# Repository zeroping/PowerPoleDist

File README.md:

# PowerPoleDist

An Anderson PowerPole DC power distribution box.

## What is this thing?

Amateur radio hobbyists (among others) have lots of electronic gear running off of 12 VDC, and to keep the wiring a little cleaner, many of them use PowerPole connectors from Anderson Power Products. These handy little connectors can handle up to 45 amps, and have become a defacto standard.

One of the common accessories is a power breakout, basically a “power strip” for these 12 V connections. These are available from several vendors for under $100, but I wanted some slightly different features (namely, right-angle connectors), so I designed my own.

It can handle at least 30 amps, but past that, you might want to order the PCB with 2 oz/inch copper, or solder copper wires to the PCB to lower the trace resistance.

This design is as open as I can easily make it, so if you want to change something, add something, etc, you can. The one catch is that I don't have the full 3D models for the case published (license issues), but I do have the resulting 2D shapes, so you can order your own case or make simple modifications.

The documentation should be viewable in [a pretty format on Github Pages](https://zeroping.github.io/PowerPoleDist/), or [directly in the GitHub project directory along side all the source files](https://github.com/zeroping/PowerPoleDist).

## What does it take to build one?

This design consists of:
- A custom circuit board that you can order online (design files provided)
- Electronic components that you can order from most suppliers (I used Digikey)
- A few harder-to-get components (the power connectors) available from more specialized shop (I used [Powerwerx](https://powerwerx.com/anderson-power-powerpole-sb-connectors))
- An aluminum case that you can order from a place like SendCutSend (design files provided)
- Some spacers and bolts and such that you can order from a mechanical parts supplier (I used McMaster-Carr)
 
It takes some through-hole soldering and some assembly, but the largest issue with the design is the shipping costs and one-time costs for the custom parts. The parts cost is around $30 per system, but you could easily spend three times that if you ordered just one of these, since you’re buying and shipping parts from five different vendors.

As a result, I think this design is most useful for someone building several for all their amateur radio friends, or someone who is looking for a design to modify or extend.

## Ordering Components

###  PCB files

The PCB production files are in the PCB/gerbers directory. You should be able to use the zip file as-is for most PCB manufacturers. I recommend the wonderful [PCB Shopper](https://pcbshopper.com/) to price-compare for a 2-layer, 40 x 130mm board. You might want to [check for any github issues](https://github.com/zeroping/PowerPoleDist/issues) before you order.

The original PCB design files are in the [PCB directory](https://github.com/zeroping/PowerPoleDist/tree/master/PCB). It's designed in the open-source PCB design package [KiCad](https://kicad.org/).

### Components

A reasonable list of the parts and costs [is available here](https://github.com/zeroping/PowerPoleDist/raw/master/Docs/PowerPole_Distribution_Board_Costs.ods).

You can order all of these parts [from Digi-Key using this cart link] (https://www.digikey.com/short/zb19f1), but you may want to order the [Anderson PowerPole parts from Powerwerx](https://powerwerx.com/anderson-power-powerpole-sb-connectors) to get better prices. The links are also in [the parts list spreadsheet](https://github.com/zeroping/PowerPoleDist/raw/master/Docs/PowerPole_Distribution_Board_Costs.ods).

You'll also want to add some [Mini/APM/ATM fuses](https://www.digikey.com/product-detail/en/eaton-bussmann-electrical-division/BK-ATM-30/283-2332-ND/264848) of whatever rating you want.

They're not necessary or 100% perfect, but I've been using [these rubber feet on Amazon](https://www.amazon.com/gp/product/B07LCMS23S/ref=ppx_yo_dt_b_search_asin_title?ie=UTF8&psc=1).

### Case

The case can be ordered by uploading the files in the [Mechanical directory](https://github.com/zeroping/PowerPoleDist/tree/master/Mechanical) to a place like [SendCutSend](https://sendcutsend.com/), in one of their 0.063” / 1.6 mm materials. I used their [5052 Aluminum](https://sendcutsend.com/aluminum/), and these are tight-fit parts, so you might want to adjust the files a tad for other materials. Be aware that they currently have a $29 minimum per material, so either order more than one, or see what else you want to get cut from metal.

There are also some M3 screws, spacers, and nuts that hold the whole thing together. I ordered these from [McMaster-Carr](https://www.mcmaster.com/), but they all come in packs of 100 – you wanted to build 25 of these, right? The links are available in [the parts list spreadsheet](https://github.com/zeroping/PowerPoleDist/raw/master/Docs/PowerPole_Distribution_Board_Costs.ods).

## Assembly

Start by putting the right-angle contacts into the Anderson PowerPole housings, and slotting the red and black housings side by side. Be sure to check which side the red goes on!

Next, solder the high-current components into the board: the PowerPole contacts, and the fuse holders. These will all take a bit of heat from your soldering iron due to the large traces, and will take lots of solder. I haven’t managed to use too much solder yet. The fuse holders particularly don’t like to wick solder to their surfaces without enough solder on them.

I recommend using some clever supporting on a heat-resistant surface to get all of these parts held in place while you solder them. You especially want to make sure the PowerPole contacts aren’t in crooked.

Then, solder all of the smaller through-hole components. This should be relatively straight forward.

The LEDs can be soldered directly on the board, or you can raise them up to get them to poke through the top of the case. If you raise them up, I recommend measuring and cutting 10 little scraps of wire insulation, and using that wire insulation to get the LEDs at the right height. Since the PCB silkscreen isn't super clear, the flat side / short leg of the LED goes away from the PowerPoles.

Decide if you want the LEDs to be on all the time, or just when you press the fuse check button. If you want them on all the time, short JP1 with some solder. Be aware, the current-limiting resistors for the LEDs were chosen to be pretty bright, so you might choose larger resistances for R1-R10 if you want them on all the time.

Also decide if you want the case connected to GND. If you do, then short jumper JP101 with some solder. I don’t recommend it, as the fuses will probably short 12V to the case if you decided to unplug one of them while the system is powered.

Next, start assembling the case. Start by threading the ‘front’ panel down between the PowerPole housings. This panel is just barely not reversible – the PowerPole housings are slight off-center and closer to the end of the board with the tactile switch. Add that to the list of fixes for the next version!

Once you have the front panel in place, you can put the top on, threading the LEDs in place as as you go. You can start to fit the front panel into the top by tapping it gently with a hammer. This aluminum will bend if you’re not careful, but it makes for a satisfyingly tight fit when it goes together.

This is now your last chance to check everything over and put the spacers in before you finish assembling the case. The taller spacers go on the top of the board, and the shorter ones go below, so put those in place, and thread the long M3 screws through the case top, the spacers, and PCB. From this point on, you will want to leave the M3 screws in place to keep the spacers lined up. You might want to  put the nuts on for now to hold them in place. It is quite annoying to have to disassemble the case to re-position a spacer.

Now, add the case back and sides. Again, you might want to use a hammer to tap them in. Use a board edge or something to let you put the "top" against a firm, flat surface, since there are now M3 screw heads sticking out of the top.

At this point, you can take the M3 nuts back off and add the case bottom. You might want to again thread the M3 nuts on to hold the screws in place while you tap the aluminum together.

Once you get the case all slotted together, you can try adding rubber feet. The ones I found don’t fit perfectly, but they squish just enough to let these nuts thread on to the M3 screw. I have found that squishing the feet (with nuts in place) just a little bit helps me get it started, and after that, the nuts seem to lock in place enough to let you tighten them. I’d like to have better feet, but these are the best ones I’ve found that are cheap.

## Issues

Github has a way to handle [reporting issues](https://github.com/zeroping/PowerPoleDist/issues), so submit any problems there, and look there for issues that other people have hit. The nice thing about handling it here is that, even if I'm not attentive, at least the issues will all be public.

## Reuse of this design

I want this design to be open for anyone to use for hobbiest use. If you’re selling them for a profit, give me some attribution and link to this git repo. If you’re selling more than 100 for a profit, let me know - I will probably still be ok with it.

I’ll work on picking a proper license at some point, but for now, just be reasonable.

## Other references

In the very least, I wanted to point out an [alternative PowerPole distribution board by Tyler Ward, M0UAV, over on hackaday.io](https://hackaday.io/project/10489-powerpole-distribution-block). His version uses the vertical PowerPole PCB terminals, and an acrylic case, but is otherwise very similar.

I know there are a fair number of amateur radio users who are using 4-cell LiFePo4 batteries for portable DC power sources, so I'll also mention [Alex Klimaj's LiPow USB-C battery charger](https://hackaday.io/project/161771-lipow-the-usb-c-lipo-battery-charger). It doesn't support LiFePo4 chemistry right out of the box, but it's an interesting and unique design that I'm likely to use in the future for charging my home-built battery pack.

If you have a related open hardware design, let me know, and I might add a link to it here.

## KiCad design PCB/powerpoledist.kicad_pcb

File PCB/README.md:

These are the files for the circuit board, designed in KiCAD 5.0.2. There are a couple of custom libraries that I made for the Anderson PowerPole right-angle connectors and the fuse holders, but they should be included here. 

Note that there are two parallel versions of many of the fust check components - this lets you build the board using either through-hole or surface-mount components, but I recommend the through-hole components if you're building the boards as one-offs.

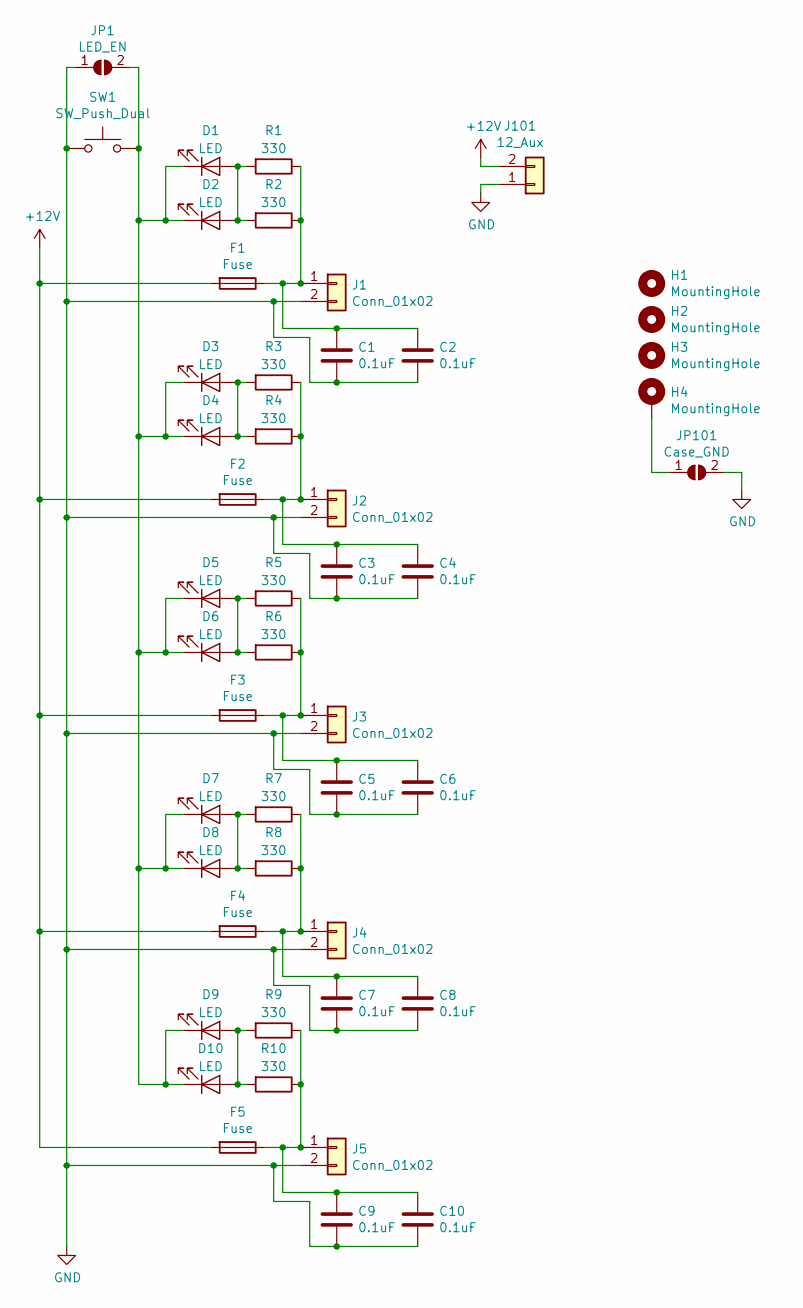
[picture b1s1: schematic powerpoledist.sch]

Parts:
C1, C3, C5, C7, C9: 0.1uF; C_0805_2012Metric_Pad1.15x1.40mm_HandSolder; MPN C0805C104M3RACTU
C2, C4, C6, C8, C10: 0.1uF; C_Disc_D3.8mm_W2.6mm_P2.50mm; MPN K104Z15Y5VE5TL2
D1, D3, D5, D7, D9: LED; D_0805_2012Metric_Pad1.15x1.40mm_HandSolder; MPN LTST-S220GKT
D2, D4, D6, D8, D10: LED; LED_D3.0mm; MPN INL-3AR30
F1, F2, F3, F4, F5: Fuse; Fuseholder_Blade_Mini_Keystone_3557_Slots; MPN 3557
H1, H2, H3, H4: MountingHole; MountingHole_3.5mm_Pad_Via
J1, J2, J3, J4, J5: Conn_01x02; PowerPole_PP45_1336G1_1x2_Horizontal; MPN 1336G1
J101: 12_Aux; PinHeader_1x02_P2.54mm_Vertical
JP1: LED_EN; SolderJumper-2_P1.3mm_Open_RoundedPad1.0x1.5mm
JP101: Case_GND; SolderJumper-2_P1.3mm_Open_RoundedPad1.0x1.5mm
R1, R3, R5, R7, R9: 330; R_0805_2012Metric_Pad1.15x1.40mm_HandSolder; MPN RMCF0805JT330R
R2, R4, R6, R8, R10: 330; R_Axial_DIN0204_L3.6mm_D1.6mm_P5.08mm_Horizontal; MPN ‎CFM14JT330R‎
SW1: SW_Push_Dual; SW_PUSH_6mm_H4.3mm; MPN MJTP1230

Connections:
+12V: F1.2, F2.2, F3.2, F4.2, F5.2, J101.2
GND: C1.2, C2.2, C3.2, C4.2, C5.2, C6.2, C7.2, C8.2, C9.2, C10.2, J1.2, J2.2, J3.2, J4.2, J5.2, J101.1, JP1.1 (A), JP101.2 (B), SW1.1
unnamed: C1.1, C2.1, F1.1, J1.1, R1.1, R2.1
unnamed: C3.1, C4.1, F2.1, J2.1, R3.1, R4.1
unnamed: C5.1, C6.1, F3.1, J3.1, R5.1, R6.1
unnamed: C7.1, C8.1, F4.1, J4.1, R7.1, R8.1
unnamed: C9.1, C10.1, F5.1, J5.1, R9.1, R10.1
unnamed: D1.1 (K), D2.1 (K), D3.1 (K), D4.1 (K), D5.1 (K), D6.1 (K), D7.1 (K), D8.1 (K), D9.1 (K), D10.1 (K), JP1.2 (B), SW1.2
unnamed: D1.2 (A), D2.2 (A), R1.2, R2.2
unnamed: D3.2 (A), D4.2 (A), R3.2, R4.2
unnamed: D5.2 (A), D6.2 (A), R5.2, R6.2
unnamed: D7.2 (A), D8.2 (A), R7.2, R8.2
unnamed: D9.2 (A), D10.2 (A), R9.2, R10.2
unnamed: H4.1, JP101.1 (A)

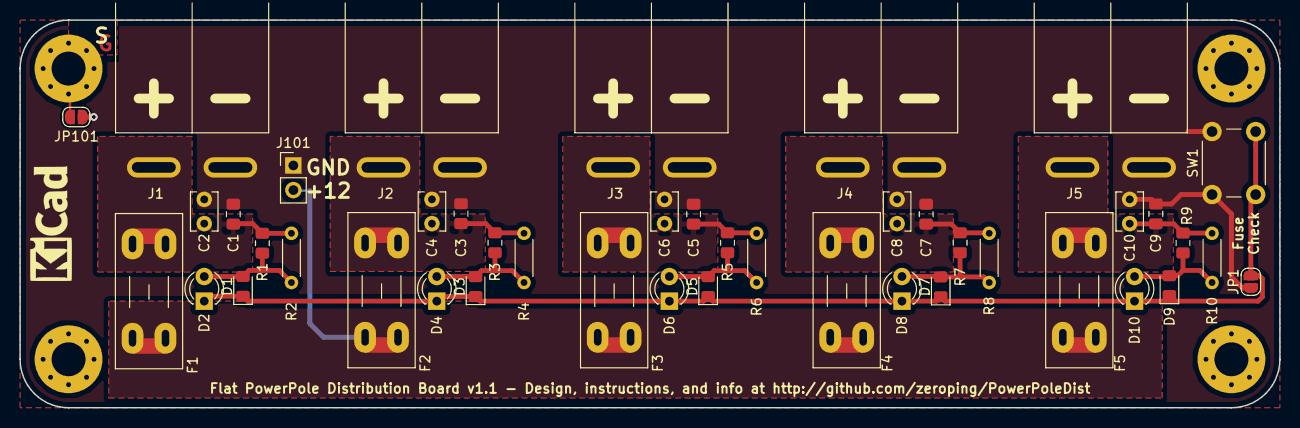
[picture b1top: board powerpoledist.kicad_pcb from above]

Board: 2 copper layers, 130.0 x 40.0 mm, 48 parts (0 on the bottom side), 14 nets.

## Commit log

2020-07-26 Initial commit of PCB files as used for board v1.1
2020-07-26 Gerber files used to produce board v1.1
2020-07-26 Added lots of documentation
2020-07-26 Added mechanical files
2020-07-26 Set theme jekyll-theme-slate
2020-07-26 Added images
2020-07-26 Testing images in the readme
2020-07-26 More readme edits and embedded images
2020-07-26 more Readme updates
2020-07-27 Typo in the readme and additions
2020-07-27 More readme typos
2020-07-29 Set theme jekyll-theme-hacker
2021-11-08 Update README.md
    https://forum.kicad.info/t/warning-avoid-all-links-to-kicad-pcb-org-use-kicad-org/31521
